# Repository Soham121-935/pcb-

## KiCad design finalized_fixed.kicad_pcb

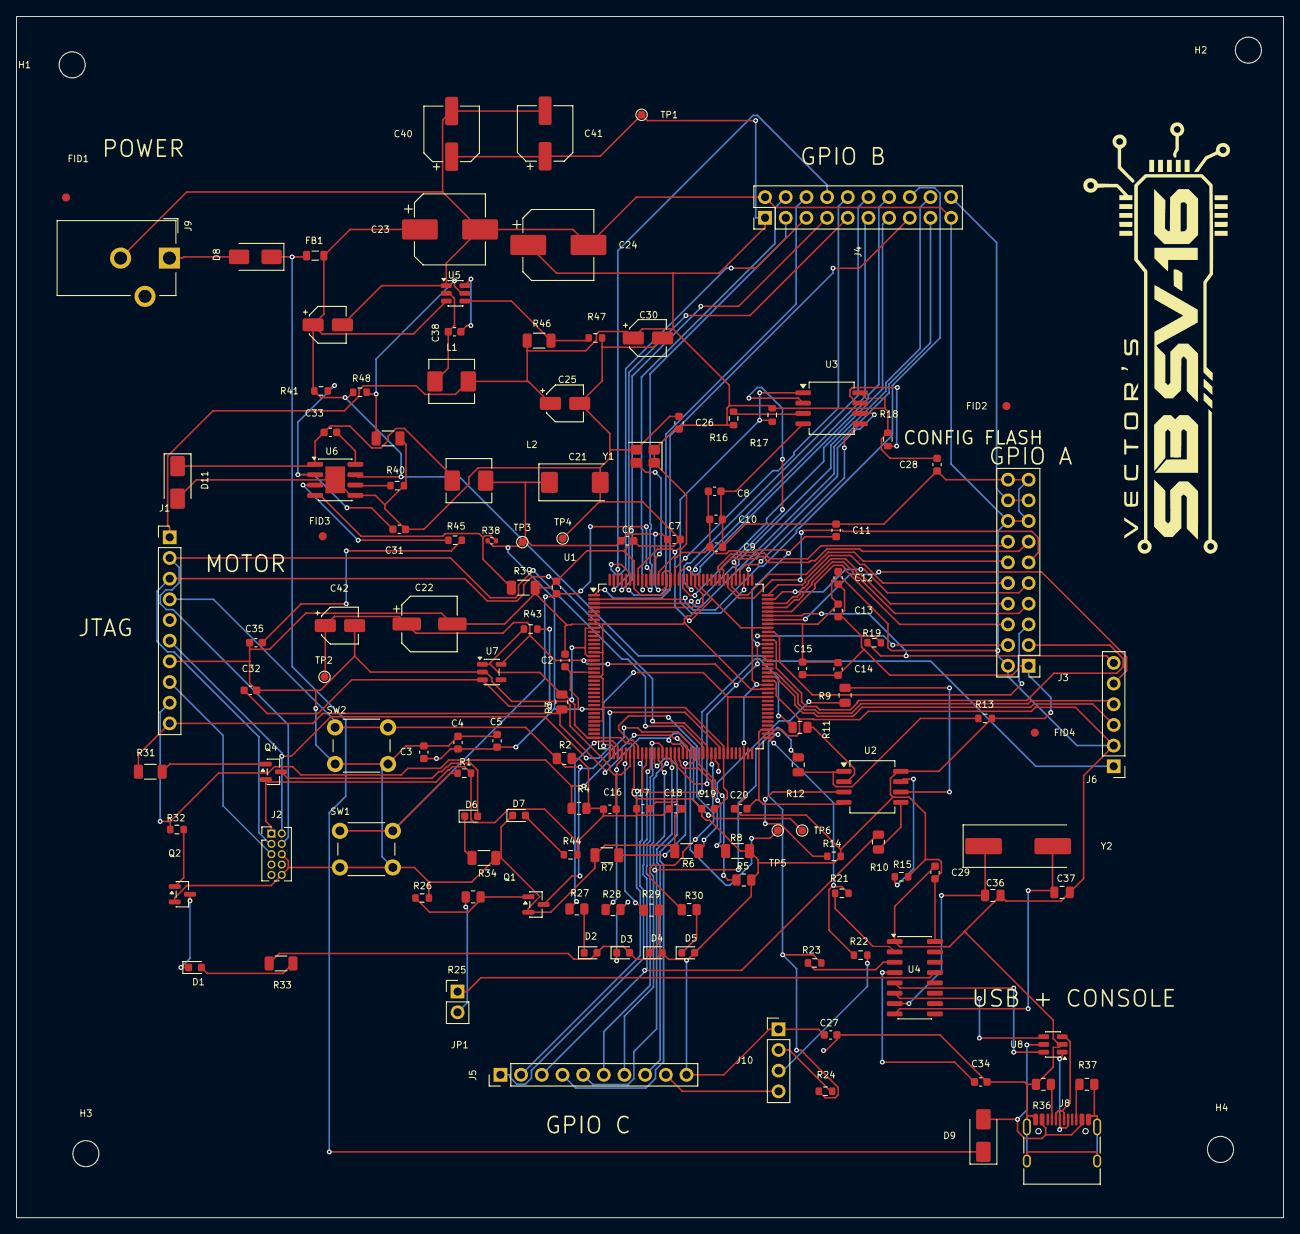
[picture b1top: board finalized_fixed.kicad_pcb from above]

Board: 4 copper layers, 155.7 x 147.6 mm, 140 parts (0 on the bottom side), 119 nets.

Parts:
C1, C2, C3, C4, C5, C6, C7, C8, C9, C10, C11, C12, C13, C14, C15, C16, C17, C18, C19, C20, C26, C27, C28, C29, C33, C34, C38: 100nF; C_0603_1608Metric
C21: 100uF 25V tant; CP_EIA-7343-31_Kemet-D
C22: 22uF 63V; CP_Elec_6.3x5.4
C23: 470uF 25V; CP_Elec_8x10.5
C24: 220uF 25V hybrid; CP_Elec_8x10.5
C25, C30: 10uF; CP_Elec_4x5.4
C31, C32: 470nF; C_0603_1608Metric
C35: 100pF; C_0603_1608Metric
C36, C37: 22pF; C_0805_2012Metric
C39, C42: 10uF 35V electrolytic; CP_Elec_4x5.4
C40, C41: 22uF 63V electrolytic; CP_Elec_6.3x5.4
D1, D2, D4, D5: LED green; LED_0603_1608Metric
D3: LED; LED_0603_1608Metric
D6, D7: LED red; LED_0603_1608Metric
D8, D9, D11: SS34; D_SMA
FB1: 600R @100MHz; L_0805_2012Metric
FID1: FID1; Fiducial_1mm_Mask2mm
FID2: FID2; Fiducial_1mm_Mask2mm
FID3: FID3; Fiducial_1mm_Mask2mm
FID4: FID4; Fiducial_1mm_Mask2mm
H1: H1; MountingHole_3.2mm_M3
H2: H2; MountingHole_3.2mm_M3
H3: H3; MountingHole_3.2mm_M3
H4: H4; MountingHole_3.2mm_M3
J1: JTAG; PinHeader_1x10_P2.54mm_Vertical
J2: JTAG-1.27; PinHeader_2x05_P1.27mm_Vertical
J3: EXP-A; PinHeader_2x10_P2.54mm_Vertical
J4: EXP-B; PinHeader_2x10_P2.54mm_Vertical
J5: EXP-C; PinHeader_1x10_P2.54mm_Vertical
J6: MOTOR; PinHeader_1x06_P2.54mm_Vertical
J8: USB-C; USB_C_Receptacle_HRO_TYPE-C-31-M-12
J9: 7-12 V; BarrelJack_CUI_PJ-102AH_Horizontal
J10: CONSOLE; PinHeader_1x04_P2.54mm_Vertical
JP1: DTR ENABLE; PinHeader_1x02_P2.54mm_Vertical
L1, L2: 10 uH; L_Sunlord_MWSA0518S
Q1: 2N7002; SOT-23
Q2: MMBT3904; SOT-23
Q4: MMBT3906; SOT-23
R1, R13, R14, R15, R16, R17, R18, R19, R26, R32, R47: 10k; R_0603_1608Metric
R2, R3, R4, R5, R25: 4.7k; R_0805_2012Metric
R6, R7, R8, R31, R33, R34: 1k; R_1206_3216Metric
R9, R10, R11, R12: 100R; R_0805_2012Metric
R21, R22, R23, R24: 0R; R_0603_1608Metric
R27, R28, R29, R30: 470R; R_0805_2012Metric
R36, R37: 5.1k; R_0805_2012Metric
R38: 12.4k; R_0402_1005Metric
R39, R46, R49: 33k; R_1206_3216Metric
R40, R41, R43, R48: 100k; R_0603_1608Metric
R44: 1k; R_0603_1608Metric
R45: 150k; R_0603_1608Metric
SW1: RESET; SW_PUSH_6mm
SW2: RECONFIG; SW_PUSH_6mm
TP1: 3V3; TestPoint_Pad_D1.0mm
TP2: 2V5; TestPoint_Pad_D1.0mm
TP3: 1V1; TestPoint_Pad_D1.0mm
TP4: GND; TestPoint_Pad_D1.0mm
TP5: DONE; TestPoint_Pad_D1.0mm
TP6: INITN; TestPoint_Pad_D1.0mm
U1: LFE5U-12F-6TG144C; LQFP-144_20x20mm_P0.5mm
U2, U3: W25Q64JVSSIQ; SOIC-8_5.3x6.2mm_P1.27mm
U4: CH340G; SOIC-16_3.9x9.9mm_P1.27mm
U5: AP62300TWU-7; SOT-23-6
U6: MP1584EN; SOIC-8-1EP_3.9x4.9mm_P1.27mm_EP2.41x3.3mm
U7: LP5907MFX-2.5; SOT-23-5
U8: USBLC6-2SC6; SOT-23-6
Y1: ECS-3225MV-250-BN-TR3; ECS_3225MV_3.2x2.5mm
Y2: 12 MHz (CH340G clock); Crystal_SMD_HC49-SD

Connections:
1V1: C2.1, C3.1, C4.1, C5.1, C6.1, C7.1, C21.1, L2.2, R38.1, TP3.1, U1.20, U1.29, U1.38, U1.66, U1.83, U1.130
2V5: C8.1, C9.1, C10.1, C11.1, C22.1, C42.1, TP2.1, U1.17, U1.53, U1.96, U1.132, U7.5
3V3: C12.1, C13.1, C14.1, C15.1, C16.1, C17.1, C18.1, C19.1, C20.1, C24.1, C25.1, C26.1, C27.1, C28.1, C29.1, C30.1, C40.1, C41.1, D2.2, D3.2, D4.2, D5.2, J1.1, J2.1, J3.1, J4.1, J5.10, J10.1, L1.2, Q4.2, R1.2, R2.2, R3.2, R4.2, R5.2, R8.2, R13.2, R14.2, R15.2, R16.2, R17.2, R18.2, R19.2, R33.1, R43.1, R44.1, R46.1, TP1.1, U1.9, U1.16, U1.36, U1.43, U1.70, U1.86, U1.100, U1.122, U1.137, U2.8, U3.8, U4.16, U7.1, Y1.1, Y1.4
5V_USB: J3.17, J3.18, J4.20
A0: J5.1, U1.45
A1: J5.2, R11.1, U1.46
A2: J5.3, R10.1, U1.47
A3: J5.4, U1.48
A4: J5.5, R12.1, U1.49
A5: J5.6, U1.50
A6: J5.7, U1.51
A7: J5.8, U1.52
A8: J3.3, U1.97
A9: J3.4, U1.98
A10: J3.5, U1.99
A11: J3.6, U1.104
A12: J3.7, U1.105
A13: J3.8, U1.106
A14: J3.9, U1.107
A15: J3.10, U1.108
B0: J4.3, U1.135
B1: J4.4, U1.136
B2: J4.5, U1.139
B3: J4.6, U1.140
B4: J4.7, U1.141
B5: J4.8, U1.142
B6: J4.9, U1.143
B7: J4.10, U1.128
B8: J4.11, U1.124
B9: J4.12, U1.125
B10: J4.13, U1.126
B11: J4.14, U1.127
B12: J4.15, U1.1
B13: J4.16, U1.2
B14: J4.17, U1.3
B15: J4.18, U1.4
CC1: J8.A5, R36.1
CC2: J8.B5, R37.1
CCLK: R8.1, R9.1, U1.54
CFG_0: R6.1, U1.62
CFG_1: R5.1, U1.59
CFG_2: R7.1, U1.58
D1_A: D1.2, R33.2
D6_K: D6.1, R34.1
D7_A: D7.2, R44.2
DONE: J1.9, R4.1, R32.1, TP5.1, U1.56
DTR_F: JP1.2, R25.1
FB_1V1: R38.2, R39.1, U6.4
GND: C1.2, C2.2, C3.2, C4.2, C5.2, C6.2, C7.2, C8.2, C9.2, C10.2, C11.2, C12.2, C13.2, C14.2, C15.2, C16.2, C17.2, C18.2, C19.2, C20.2, C21.2, C22.2, C23.2, C24.2, C25.2, C26.2, C27.2, C28.2, C29.2, C30.2, C31.2, C32.2, C34.2, C35.2, C36.2, C37.2, C39.2, C40.2, C41.2, C42.2, D7.1, D11.2, J1.7, J2.6, J2.10, J3.2, J3.15, J3.16, J3.19, J3.20, J4.2, J4.19, J5.9, J6.2, J8.A1, J8.A12, J8.B1, J8.B12, J8.SH, J9.2, J10.4, Q1.2, Q2.2, R6.2, R7.2, R26.2, R34.2, R36.2, R37.2, R39.2, R40.2, R47.2, R49.2, SW1.2, SW2.2, TP4.1, U1.8, U1.15, U1.21, U1.32, U1.42, U1.65, U1.75, U1.85, U1.87, U1.101, U1.123, U1.129, U1.131, U1.138, U2.4, U3.4, U4.1, U5.1, U6.5, U6.9, U7.2, U8.2, Y1.2
INITN: J1.10, R3.1, R31.1, TP6.1, U1.55
J9_VIN: D8.2, J9.1
J10_RX: J10.3, R22.2
J10_TX: J10.2, R24.2
PROGRAMN: J1.4, Q1.3, R2.1, SW2.1, U1.57
Q1_G: Q1.1, R25.2, R26.1
Q2_B: Q2.1, R32.2
Q2_C: D1.1, Q2.3
Q4_B: Q4.1, R31.2
Q4_C: D6.2, Q4.3
TCK: J1.8, J2.5, U1.63
TDI: J1.3, J2.3, U1.61
TDO: J1.2, J2.4, U1.60
TMS: J1.6, J2.2, U1.64
U2_CLK: R9.2, U2.6
U2_CS: R12.2, R13.1, U2.1
U2_DI: R10.2, U2.5
U2_DO: R11.2, U2.2
U2_HOLD: R15.1, U2.7
U2_WP: R14.1, U2.3
U3_HOLD: R18.1, U3.7
U3_WP: R17.1, U3.3
U4_DTR: JP1.1, U4.13
U4_RXD: R23.1, U4.3
U4_TXD: R21.1, U4.2
U4_V3: C34.1, U4.4
U5_BST: C38.1, U5.6
U5_EN: R48.2, R49.1, U5.5
U5_FB: R46.2, R47.1, U5.4
U5_SW: C38.2, L1.1, U5.2
U6_BST: C33.1, U6.8
U6_COMP: R45.1, U6.3
U6_COMP_RC: C35.1, R45.2
U6_EN: C31.1, R41.2, U6.2
U6_FREQ: R40.1, U6.6
U6_SW: C33.2, D11.1, L2.1, U6.1
U7_EN: C32.1, R43.2, U7.3
USB_DN: J8.A7, J8.B7, U8.3
USB_DN_F: U4.6, U8.4
USB_DP: J8.A6, J8.B6, U8.1
USB_DP_F: U4.5, U8.6
USB_VBUS: D9.2, J8.A4, J8.A9, J8.B4, J8.B9, U8.5
VM_IN: C23.1, C39.1, FB1.2, J6.1, R41.1, R48.1, U5.3, U6.7
VM_IN_RAW: D8.1, D9.1, FB1.1
Y2_XI: C36.1, U4.7, Y2.1
Y2_XO: C37.1, U4.8, Y2.2
clk_25m: U1.133, Y1.3
ext_rst_n: C1.1, R1.1, SW1.1, U1.134
flash_cs_n: R16.1, U1.111, U3.1
flash_miso: U1.113, U3.2
flash_mosi: U1.112, U3.5
flash_sck: U1.110, U3.6
led0: R27.1, U1.39
led0_k: D2.1, R27.2
led1: R28.1, U1.40
led1_k: D3.1, R28.2
led2: R29.1, U1.41
led2_k: D4.1, R29.2
led3: R30.1, U1.44
led3_k: D5.1, R30.2
motor_dir1: J6.4, U1.89
motor_dir2: J6.5, U1.102
motor_fault_n: J6.6, R19.1, U1.103
pwm_out: J6.3, U1.88
spi0_cs_n: J3.11, U1.115
spi0_miso: J3.14, U1.117
spi0_mosi: J3.13, U1.116
spi0_sck: J3.12, U1.114
uart_rx: R21.2, R22.1, U1.73
uart_tx: R23.2, R24.1, U1.74

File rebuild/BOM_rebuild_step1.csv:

Ref,Spec part,Board value (step1),Footprint (board),Bought (cart),Status
U1,LFE5U-12F-6TG144C,LFE5U-12F-6TG144C,LQFP-144,0,BUY (FPGA)
U2,W25Q64JVSSIQ,W25Q64JVSSIQ,SOIC-8 5.3x6.2,1,OK (have 1 of 1)
U3,W25Q64JVSSIQ,W25Q64JVSSIQ,SOIC-8 5.3x6.2,1,BUY 1 more (need 2 total)
Y1,Active 25 MHz XO 3.2x2.5 4-pad (YIC OSC25M-3.3I/S3-25T),25 MHz ACTIVE XO,ASE-4Pin 3.2x2.5,0 active (3 passive 25 MHz HC49/US crystals bought - NOT usable here),BUY active XO
Y2,"12 MHz crystal HC49/U surface mount (passive 2-pin, OK for CH340G)",12 MHz,HC49-4H (THT) - change to SMD HC49/US,0,BUY 12 MHz SMD crystal; PENDING footprint change to SMD HC49
U4,CH340G,CH340G,SOIC-16,1,OK
U5,AP62300TWU-7,AP62300TWU-7,SOT-23-6,1,OK
U6,MP1584EN,MP1584EN,SOIC-8-1EP,1,OK
U7,LP5907MFX-2.5,LP5907MFX-2.5,SOT-23-5,1,OK
U8,USBLC6-2SC6,USBLC6-2SC6,SOT-23-6,4,OK
Q1,2N7002,2N7002,SOT-23,7,OK
Q2,MMBT3904,MMBT3904 (changed),SOT-23,9,OK
Q4,MMBT3906,MMBT3906 (changed),SOT-23,13,OK
D1-D5,LED green 0603,LED green,0603,7,OK
D6,LED red 0603 (DNP by default per spec),LED red,0603,6,OK - mark DNP on board (not done yet)
D7,LED red 0603,LED red,0603,6,OK
D8,SS34,SS34,SMA,2,BUY 1 more (need 3 total with D9/D11)
D9,SS34,SS34,SMA,2,(see D8)
D11,SS34 (1V1 catch diode),SS34,SMA,2,(see D8)
L1,10 uH CD54 >=1.5A,10 uH,SWPA6045S footprint (spec: MWSA0518) - footprint NOT changed,2 (CD54 10uH),OK value; footprint change pending
L2,10 uH CD54 >=1.5A,10 uH,SWPA6045S footprint (spec: MWSA0518) - footprint NOT changed,2 (CD54 10uH),OK value; footprint change pending
FB1,600R @100MHz 0603,600R @100MHz,0603,0,NOT BOUGHT (solder-bridge option, or buy)
C21,100uF 25V D-case tant,100uF 25V tant,CP_EIA-7343-31,1,OK
C22,22uF 63V electrolytic,22uF 63V electrolytic,CP_Elec_6.3x5.4,22,OK
C23,470uF 16V electrolytic,470uF 16V,CP_Elec_8x10.5,11,OK
C24,220uF 25V hybrid,220uF 25V hybrid,CP_Elec_8x10.5,11,OK
C25,10uF 0805 ceramic (spec) -> 10uF 35V electrolytic (decision),10uF,C_0805 - footprint NOT changed,11 (10uF 35V electrolytic),footprint change pending (CP_Elec_4x5.4)
C30,10uF 0805 ceramic (spec) -> 10uF 35V electrolytic (decision),10uF,C_0805 - footprint NOT changed,11,footprint change pending
C39,10uF electrolytic (decision),10uF 35V electrolytic,CP_Elec_4x5.4,11,OK
C40,22uF electrolytic (decision),22uF 63V electrolytic,CP_Elec_6.3x5.4,22,OK
C41,22uF electrolytic (decision),22uF 63V electrolytic,CP_Elec_6.3x5.4,22,OK
C42,10uF electrolytic (decision),10uF 35V electrolytic,CP_Elec_4x5.4,11,OK
C32,470nF 0603 (spec),470nF,C_0805 - footprint NOT changed,20 (470nF 0603),footprint change pending (0603)
C34,not in spec,100nF,0603,40,UNDECIDED (remove or leave)
C35,not in spec,100pF,0603,0,UNDECIDED (remove or leave)
C36,22pF C0G 0805 50V 5% (YAGEO CC0805JRNPO9BN220),22pF,0603 - change to 0805,0,BUY 22 pF 0805 C0G; PENDING footprint change 0603->0805
C37,22pF C0G 0805 50V 5% (YAGEO CC0805JRNPO9BN220),22pF,0603 - change to 0805,0,BUY (see C36); PENDING footprint change 0603->0805
C1-C20,100nF 0603,100nF,0603,40 (shared),OK
C26-C29,100nF 0603,100nF,0603,(shared),OK
C31,470nF 0603,470nF,0603,(shared),OK
C33,100nF 0603,100nF,0603,(shared),OK
C38,100nF 0603,100nF,0603,(shared),OK
R1,10k 0603 5% (YAGEO RC0603JR-0710KL),10k,0603,0,BUY 10k 0603 (Yageo RC0603JR-0710KL)
R2-R4,4.7k 0805,4.7k (changed),0805,(4.7k 0805 pack),OK
R5,4.7k 0805 (from bought pack),4.7k,0603 - change to 0805,(4.7k 0805 pack),PENDING footprint change 0603->0805; use bought 4.7k 0805 pack
R6-R8,1k 1206 (from bought pack),1k,0603 - change to 1206,(1k 1206 pack),PENDING footprint change 0603->1206; use bought 1k 1206 pack
R9-R12,100R 1206 (spec) - board 1206,100R (changed),1206,(100R 0805 pack bought),footprint change to 0805 pending (bought 0805)
R13-R19,10k 0603 5% (YAGEO RC0603JR-0710KL),10k,0603,0,"BUY 10k 0603 (Yageo RC0603JR-0710KL), 7 pieces"
R21-R24,0R,0R (changed),0603,0,solder-bridge option (no purchase needed)
R25,4.7k 0805 (from bought pack),4.7k,0603 - change to 0805,(4.7k 0805 pack),PENDING footprint change 0603->0805; use bought 4.7k 0805 pack
R26,10k 0603 5% (YAGEO RC0603JR-0710KL),10k,0603,0,BUY 10k 0603 (Yageo RC0603JR-0710KL)
R27-R30,470R 0805,470R (changed),0805,(470R 0805 pack),OK
R31,1k 1206,1k (changed),1206,1 (1k 1206 pack),OK
R32,10k 0603 5% (YAGEO RC0603JR-0710KL),10k,0603,0,BUY 10k 0603 (Yageo RC0603JR-0710KL)
R33,1k 1206,1k (changed),1206,(1k 1206 pack),OK
R34,1k 1206,1k (changed),1206,(1k 1206 pack),OK
R36,5.1k 0805,5.1k (changed),0805,(5.1k 0805 pack),OK
R37,5.1k 0805,5.1k (changed),0805,(5.1k 0805 pack),OK
R38,12.4k 0402,12.4k (changed),0402,30,OK
R39,33k 1206,33k (changed),1206,(33k 1206 pack),OK
R40,100k 0603,100k (changed),0603,11 (thin film),OK
R41,100k 0603,100k (changed),0603,(shared),OK
R43,100k 0603,100k (changed),0603,(shared),OK
R44,not in spec,R44 (no value),0603,-,UNDECIDED
R45,not in spec,100k,0603,(shared),UNDECIDED (not in spec)
R46,33k 1206,33k (changed),1206,(shared),OK
R47,"10k 0603 1% (YAGEO RC0603FR-0710KL, 1%)",10k,1206 - change to 0603,0,BUY 10k 0603 1% (Yageo RC0603FR-0710KL); PENDING footprint change 1206->0603
R48,AP62300 EN divider (value not given in spec),100k,0603,(shared),UNDECIDED
R49,AP62300 EN divider (value not given in spec),33k,1206,(shared),UNDECIDED
J1,"Standard 2.54 mm straight male pin header, 1x10 (most available). Footprint unchanged.",JTAG,2.54mm 1x10,0,USER HAS (not in screenshots) - confirm
J2,Spec: 1.27 mm 2x5 box header. Less common; leave unpopulated and use J1 (spec option).,JTAG-1.27,1.27mm 2x5,0,OPTIONAL
J3,"Standard 2.54 mm straight male pin header, 2x10 (most available). Footprint unchanged.",EXP-A,2.54mm 2x10,0,USER HAS (not in screenshots) - confirm
J4,"Standard 2.54 mm straight male pin header, 2x10 (most available). Footprint unchanged.",EXP-B,2.54mm 2x10,0,USER HAS (not in screenshots) - confirm
J5,"Standard 2.54 mm straight male pin header, 1x10 (most available). Footprint unchanged.",EXP-C,2.54mm 1x10,0,USER HAS (not in screenshots) - confirm
J6,"Standard 2.54 mm straight male pin header, 1x6 (most available). Spec says keyed: add keying notch, or use a shrouded 1x6 header.",MOTOR,2.54mm 1x6,0,USER HAS (not in screenshots) - confirm
J7,"Standard 2.54 mm straight male pin header, 2x25 (footprint only, not fitted).",absent,-,0,ADD footprint (not fitted)
J8,USB-C 16-pin HRO,USB-C,HRO TYPE-C-31-M-12,4,OK
J9,Barrel jack 5.5/2.1,7-12 V,CUI PJ-102AH,0,USER HAS (not in screenshots) - confirm
J10,"Standard 2.54 mm straight male pin header, 1x4 (most available). Footprint unchanged.",CONSOLE,2.54mm 1x4,0,USER HAS (not in screenshots) - confirm
JP1,"Standard 2.54 mm straight male pin header, 1x2, with shunt (most available). Footprint unchanged.",DTR ENABLE,1x02,0,USER HAS (not in screenshots) - confirm
SW1,6x6 tact,RESET,SW_PUSH_6mm,0,USER HAS (not in screenshots) - confirm
SW2,6x6 tact,RECONFIG,SW_PUSH_6mm,0,USER HAS (not in screenshots) - confirm
TP1-TP6,1 mm pads,OK,TestPoint,-,OK
H1-H4,M3 mount holes,OK,-,-,OK

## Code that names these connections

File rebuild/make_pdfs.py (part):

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  'U6 COMP network: change R45 from 10k to 150k, and C35 from 100 nF to 100 pF. Calculated with the MP1584EN datasheet method: fsw 911 kHz (R40 = 100k), crossover about 91 kHz, output C21 = 100 uF, Vout 1.1 V. At 10k the crossover would be about 6 kHz, far below the expected range.',
  'U6 COMP second capacitor (C6 on COMP): do NOT fit. The datasheet table lists no second COMP capacitor for low output voltages. Verify loop stability on the bench.',
  'C23 (470 uF input bulk): change the voltage to 25 V (electrolytic, CP_Elec_8x10.5). 16 V on a 12 V rail is 75% of rated voltage, too close to the limit.',
  '5V_USB: connect this net to USB_VBUS in the schematic. The spec says the 5 V pins on J3 (17, 18) and J4 (20) are USB VBUS only. Right now 5V_USB has no source, so those pins are unpowered.',
  'U5 (AP62300) FB: keep the divider, R46 = 33k from 3V3 to U5_FB and R47 = 10k from U5_FB to GND. Do NOT connect U5_FB to 3V3. Output = 0.763 x (1 + 33/10) = 3.28 V. The spec correction that said to tie FB to 3V3 is wrong for this part.',
 ]),
 ('C. Values to set (check these in KiCad after the schematic is updated)', [
  'R44 = 1k (LED D7 current limit, 3V3 to D7). Keep.',
  'R48 = 100k (EN top, VM_IN to U5_EN), R49 = 33k (EN bottom). Keep. At 12 V, EN = 2.98 V, under the 6 V EN pin limit. EN threshold 1.2 V typ (Diodes DS41958), so the buck starts at about 4.7 to 4.9 V VIN.',
  'C34 = 100 nF (CH340G V3 decoupling). Keep.',
  'R38 = 12.4k, R39 = 33k: U6 feedback. Output = 0.8 x (1 + 12.4/33) = 1.10 V. Keep.',
  'Q2 = MMBT3904 and Q4 = MMBT3906 (SOT-23, pinout per spec). C36, C37 = 22 pF.',
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  'PASS: LP5907 (U7): EN delay R43 100k + C32 470 nF. The 2V5 switch matches the spec correction 4 (Q3 and R42 removed).',
  'PASS: USB-C (J8): CC1/CC2 each have a 5.1k pull-down (R36, R37). VBUS to VM_IN_RAW through D9 and FB1. D+/D- through the USBLC6 array (U8) to the CH340G.',
  'PASS: CH340G (U4, keep this part): VCC on 3V3, 12 MHz crystal Y2 with 22 pF C36/C37, V3 decoupling C34, USB D+/D- on pins 5/6.',
  'PASS: Y1 pinout matches the ECS-3225MV (1 enable tied to 3V3, 2 GND, 3 clk_25m, 4 VDD on 3V3).',
  'PASS: flash U2/U3 WP and HOLD pins have pull-ups to 3V3 (R14, R15, R17, R18).',
  'ACTION: 5V_USB is not tied to USB_VBUS. See B.',
  'ACTION: R45 = 10k and C35 = 100 nF in the schematic. See B.',
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  'Schematic: change R45 from 10k to 150k (COMP resistor).',
  'Schematic: change C35 from 100 nF to 100 pF (COMP capacitor).',
  'Schematic: change C23 to 25 V.',
  'Schematic: connect 5V_USB to USB_VBUS (5 V header pins are VBUS only).',
  'Footprint: confirm the Y1 ECS land pattern (1.4 x 1.2 mm, centres +-1.10 / +-0.80 mm) against the ECS drawing.',
  'Datasheet: CH340G pin 15 (R232) and the unused modem pins 9-12, 14.',
  'Datasheet: LP5907 pin 4 (BYP) is unconnected in the schematic. Confirm it can stay open.',
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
